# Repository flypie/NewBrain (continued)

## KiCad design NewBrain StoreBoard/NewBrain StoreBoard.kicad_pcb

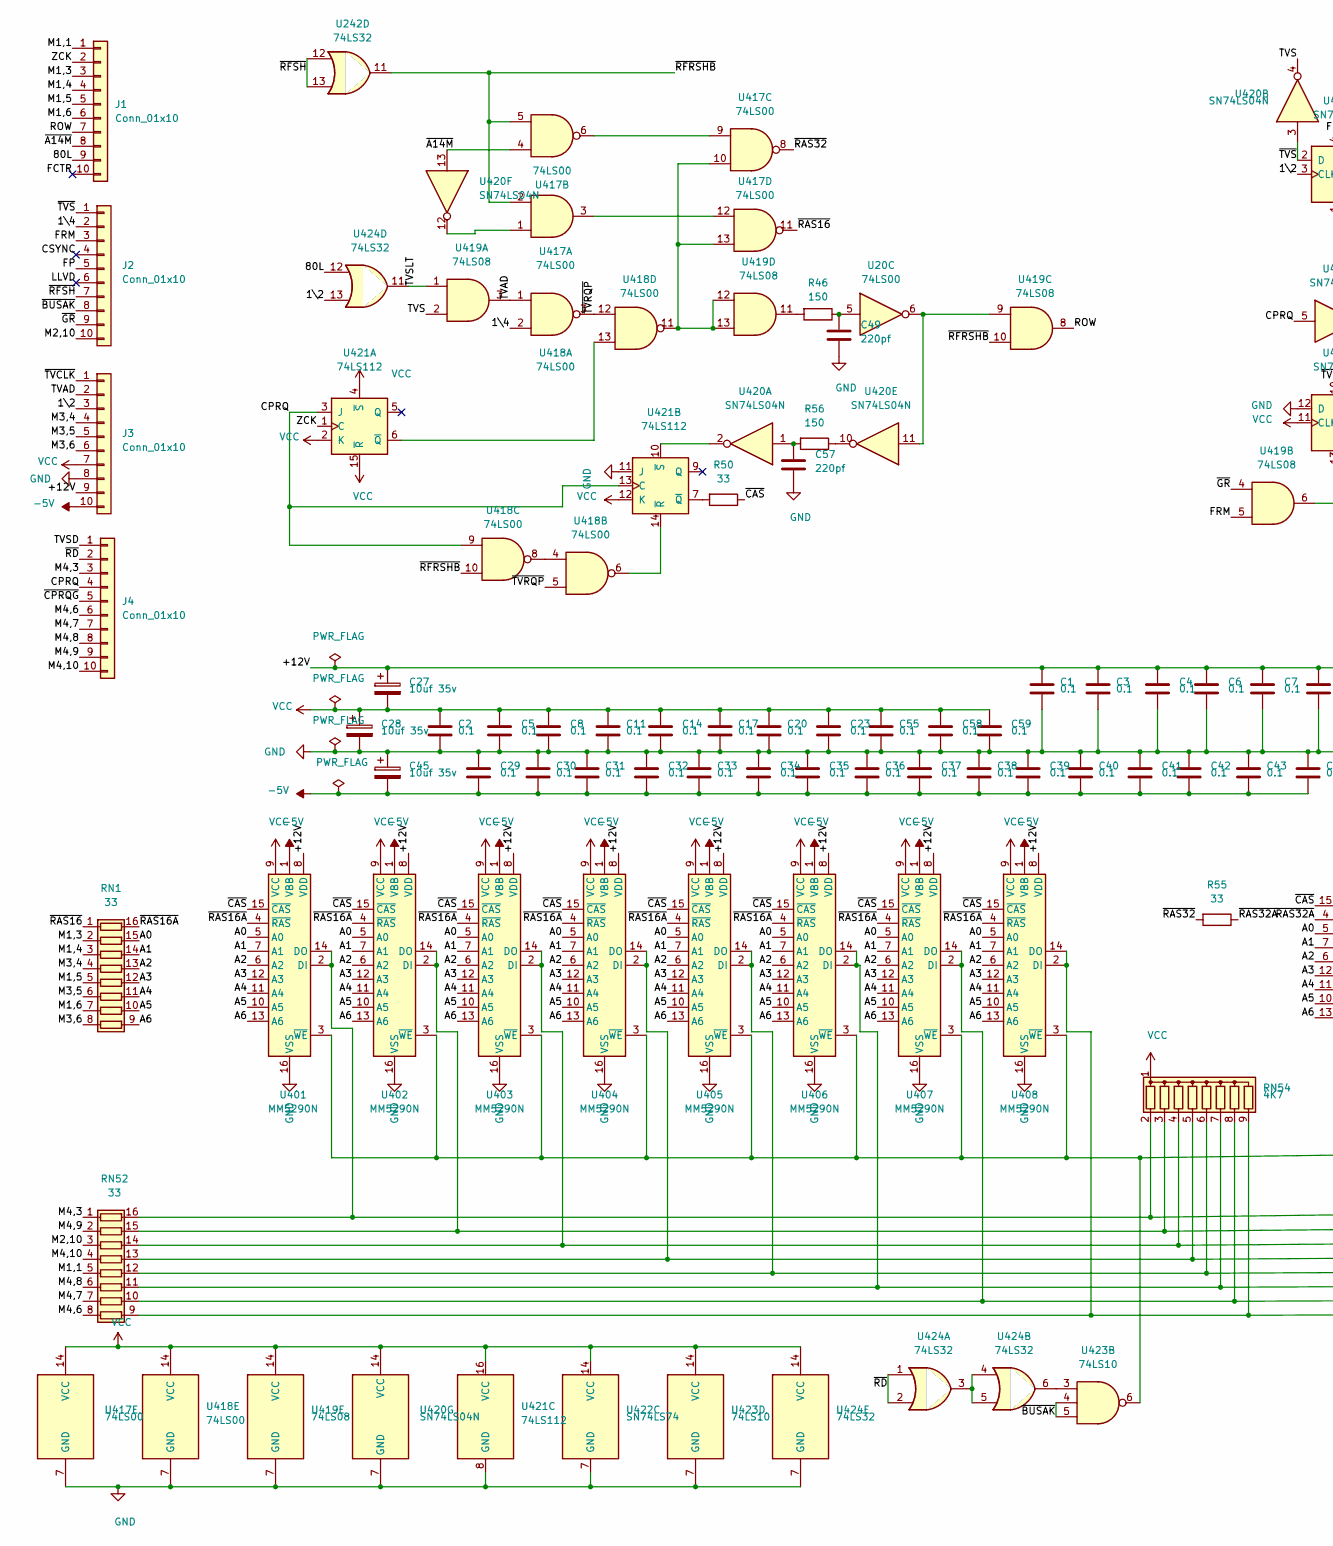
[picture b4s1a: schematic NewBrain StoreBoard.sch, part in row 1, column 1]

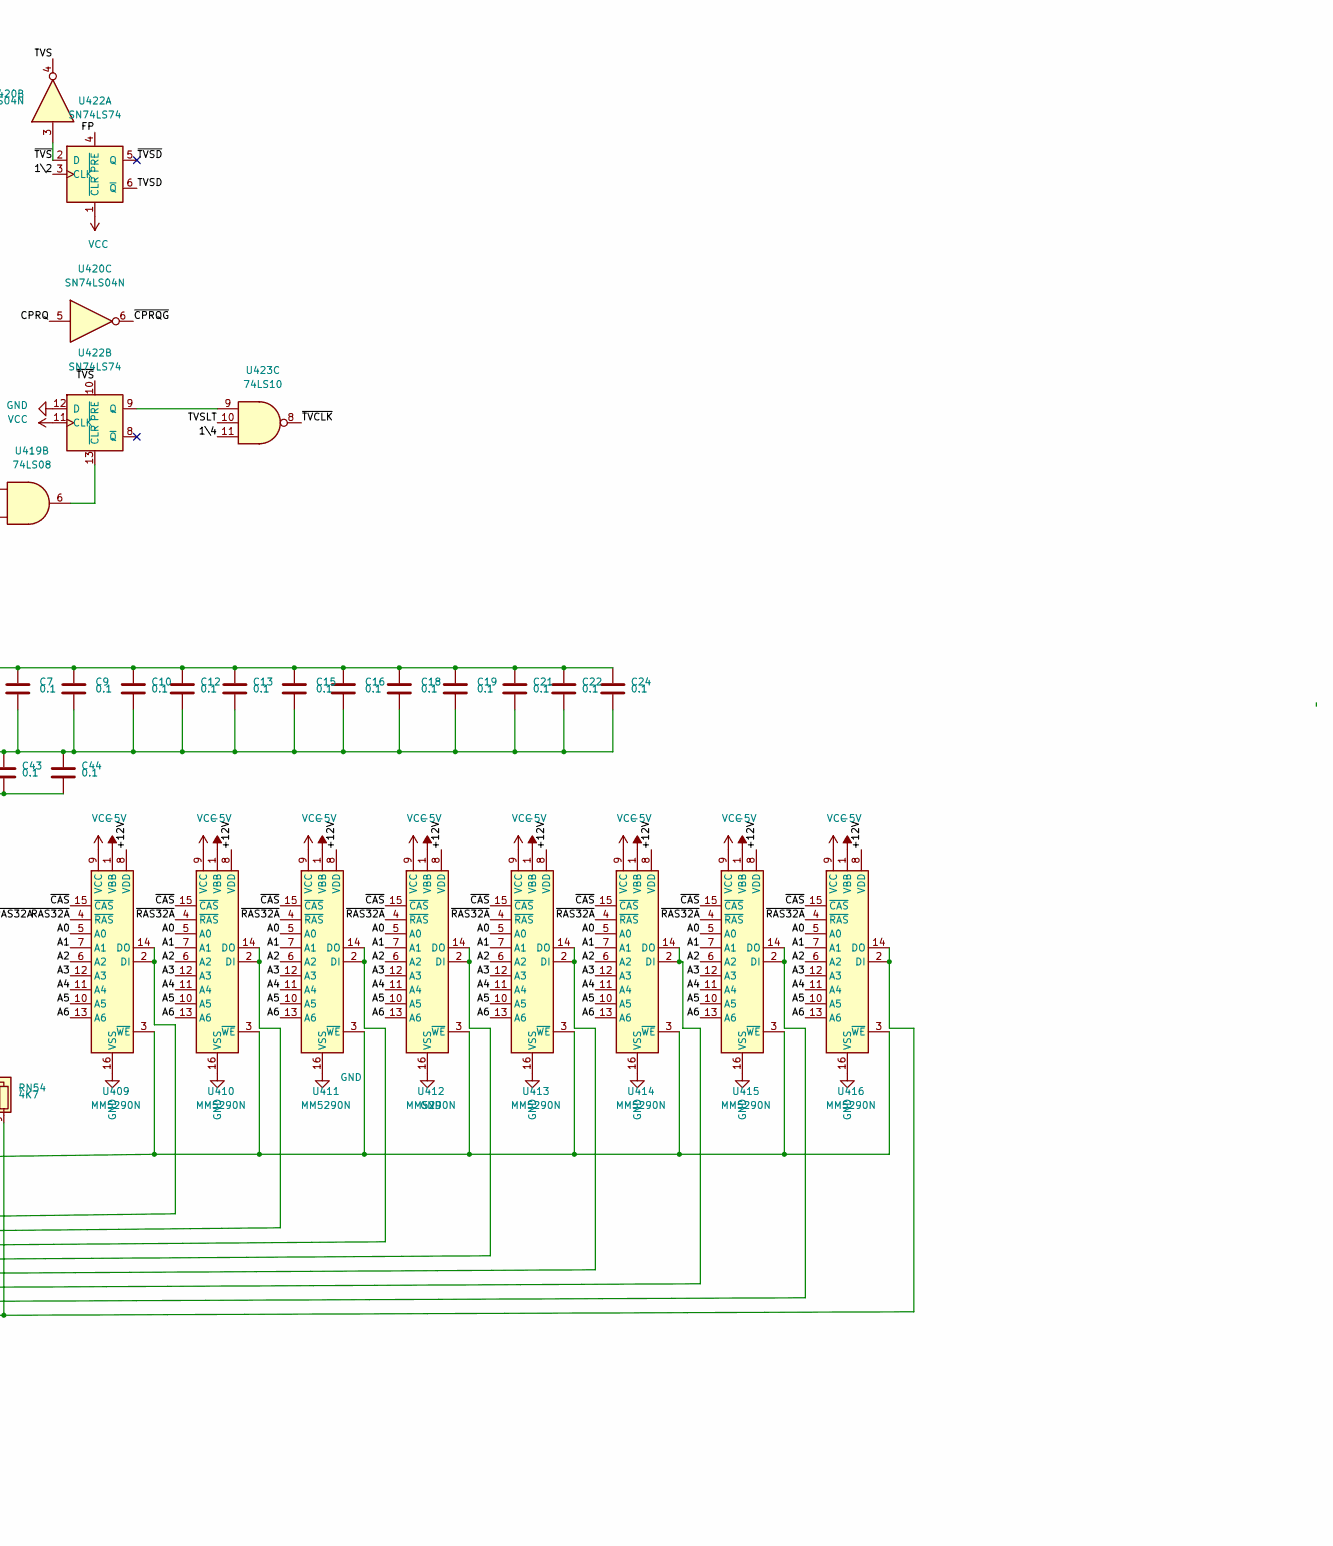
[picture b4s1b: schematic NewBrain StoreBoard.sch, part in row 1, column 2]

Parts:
C1, C2, C3, C4, C5, C6, C7, C8, C9, C10, C11, C12, C13, C14, C15, C16, C17, C18, C19, C20, C21, C22, C23, C24, C29, C30, C31, C32, C33, C34, C35, C36, C37, C38, C39, C40, C41, C42, C43, C44, C55, C58, C59: 0.1; C_Disc_D3.0mm_W1.6mm_P2.50mm
C27, C28, C45: 10uf 35v; CP_Radial_D5.0mm_P2.00mm
C49, C57: 220pf; C_Disc_D3.0mm_W1.6mm_P2.50mm
J1, J2, J3, J4: Conn_01x10; JST_EH_B10B-EH-A_1x10_P2.50mm_Vertical
R46, R56: 150; R_Axial_DIN0204_L3.6mm_D1.6mm_P2.54mm_Vertical
R50, R55: 33; R_Axial_DIN0204_L3.6mm_D1.6mm_P2.54mm_Vertical
RN1, RN52: 33; DIP-16_W7.62mm
RN54: 4K7; R_Array_SIP9
U20, U417, U418: 74LS00; DIP-16_W7.62mm
U242, U424: 74LS32; DIP-16_W7.62mm
U401, U402, U403, U404, U405, U406, U407, U408, U409, U410, U411, U412, U413, U414, U415, U416: MM5290N; DIP-16_W7.62mm
U419: 74LS08; DIP-16_W7.62mm
U420: SN74LS04N; DIP-16_W7.62mm
U421: 74LS112; DIP-16_W7.62mm
U422: SN74LS74; DIP-16_W7.62mm
U423: 74LS10; DIP-16_W7.62mm

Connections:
-5V: C29.2, C30.2, C31.2, C32.2, C33.2, C34.2, C35.2, C36.2, C37.2, C38.2, C39.2, C40.2, C41.2, C42.2, C43.2, C44.2, C45.2, J3.10, U401.1 (VBB), U402.1 (VBB), U403.1 (VBB), U404.1 (VBB), U405.1 (VBB), U406.1 (VBB), U407.1 (VBB), U408.1 (VBB), U409.1 (VBB), U410.1 (VBB), U411.1 (VBB), U412.1 (VBB), U413.1 (VBB), U414.1 (VBB), U415.1 (VBB), U416.1 (VBB)
/1\2: J3.3, U422.3 (CLK), U424.13
/1\4: J2.2, U418.2, U423.11
/80L: J1.9, U424.12
/+12V: C1.1, C3.1, C4.1, C6.1, C7.1, C9.1, C10.1, C12.1, C13.1, C15.1, C16.1, C18.1, C19.1, C21.1, C22.1, C24.1, C27.1, J3.9, U401.8 (VDD), U402.8 (VDD), U403.8 (VDD), U404.8 (VDD), U405.8 (VDD), U406.8 (VDD), U407.8 (VDD), U408.8 (VDD), U409.8 (VDD), U410.8 (VDD), U411.8 (VDD), U412.8 (VDD), U413.8 (VDD), U414.8 (VDD), U415.8 (VDD), U416.8 (VDD)
/A0: RN1.15 (R2.2), U401.5 (A0), U402.5 (A0), U403.5 (A0), U404.5 (A0), U405.5 (A0), U406.5 (A0), U407.5 (A0), U408.5 (A0), U409.5 (A0), U410.5 (A0), U411.5 (A0), U412.5 (A0), U413.5 (A0), U414.5 (A0), U415.5 (A0), U416.5 (A0)
/A1: RN1.14 (R3.2), U401.7 (A1), U402.7 (A1), U403.7 (A1), U404.7 (A1), U405.7 (A1), U406.7 (A1), U407.7 (A1), U408.7 (A1), U409.7 (A1), U410.7 (A1), U411.7 (A1), U412.7 (A1), U413.7 (A1), U414.7 (A1), U415.7 (A1), U416.7 (A1)
/A2: RN1.13 (R4.2), U401.6 (A2), U402.6 (A2), U403.6 (A2), U404.6 (A2), U405.6 (A2), U406.6 (A2), U407.6 (A2), U408.6 (A2), U409.6 (A2), U410.6 (A2), U411.6 (A2), U412.6 (A2), U413.6 (A2), U414.6 (A2), U415.6 (A2), U416.6 (A2)
/A3: RN1.12 (R5.2), U401.12 (A3), U402.12 (A3), U403.12 (A3), U404.12 (A3), U405.12 (A3), U406.12 (A3), U407.12 (A3), U408.12 (A3), U409.12 (A3), U410.12 (A3), U411.12 (A3), U412.12 (A3), U413.12 (A3), U414.12 (A3), U415.12 (A3), U416.12 (A3)
/A4: RN1.11 (R6.2), U401.11 (A4), U402.11 (A4), U403.11 (A4), U404.11 (A4), U405.11 (A4), U406.11 (A4), U407.11 (A4), U408.11 (A4), U409.11 (A4), U410.11 (A4), U411.11 (A4), U412.11 (A4), U413.11 (A4), U414.11 (A4), U415.11 (A4), U416.11 (A4)
/A5: RN1.10 (R7.2), U401.10 (A5), U402.10 (A5), U403.10 (A5), U404.10 (A5), U405.10 (A5), U406.10 (A5), U407.10 (A5), U408.10 (A5), U409.10 (A5), U410.10 (A5), U411.10 (A5), U412.10 (A5), U413.10 (A5), U414.10 (A5), U415.10 (A5), U416.10 (A5)
/A6: RN1.9 (R8.2), U401.13 (A6), U402.13 (A6), U403.13 (A6), U404.13 (A6), U405.13 (A6), U406.13 (A6), U407.13 (A6), U408.13 (A6), U409.13 (A6), U410.13 (A6), U411.13 (A6), U412.13 (A6), U413.13 (A6), U414.13 (A6), U415.13 (A6), U416.13 (A6)
/CPRQ: J4.4, U418.9, U420.5, U421.3 (J), U421.13 (C)
/CSYNC: J2.4
/FCTR: J1.10
/FP: J2.5, U422.4 (~PRE)
/FRM: J2.3, U419.5
/LLVD: J2.6
/M1,1: J1.1, RN52.5 (R5.1)
/M1,3: J1.3, RN1.2 (R2.1)
/M1,4: J1.4, RN1.3 (R3.1)
/M1,5: J1.5, RN1.5 (R5.1)
/M1,6: J1.6, RN1.7 (R7.1)
/M2,10: J2.10, RN52.3 (R3.1)
/M3,4: J3.4, RN1.4 (R4.1)
/M3,5: J3.5, RN1.6 (R6.1)
/M3,6: J3.6, RN1.8 (R8.1)
/M4,3: J4.3, RN52.1 (R1.1)
/M4,6: J4.6, RN52.8 (R8.1)
/M4,7: J4.7, RN52.7 (R7.1)
/M4,8: J4.8, RN52.6 (R6.1)
/M4,9: J4.9, RN52.2 (R2.1)
/M4,10: J4.10, RN52.4 (R4.1)
/ROW: J1.7, U419.8
/TVAD: J3.2, U418.1, U419.3
/TVS: U419.2, U420.4
/TVSD: J4.1, U422.6 (~Q)
/TVSLT: U419.1, U423.10, U424.11
/ZCK: J1.2, U421.1 (C)
/~A14M: J1.8, U417.4, U420.13
/~BUSAK: J2.8, U423.4, U423.5
/~CAS: R50.1, U401.15 (~CAS), U402.15 (~CAS), U403.15 (~CAS), U404.15 (~CAS), U405.15 (~CAS), U406.15 (~CAS), U407.15 (~CAS), U408.15 (~CAS), U409.15 (~CAS), U410.15 (~CAS), U411.15 (~CAS), U412.15 (~CAS), U413.15 (~CAS), U414.15 (~CAS), U415.15 (~CAS), U416.15 (~CAS)
/~CPRQG: J4.5, U420.6
/~GR: J2.9, U419.4
/~RAS16: RN1.1 (R1.1), U417.11
/~RAS16A: RN1.16 (R1.2), U401.4 (~RAS), U402.4 (~RAS), U403.4 (~RAS), U404.4 (~RAS), U405.4 (~RAS), U406.4 (~RAS), U407.4 (~RAS), U408.4 (~RAS)
/~RAS32: R55.2, U417.8
/~RAS32A: R55.1, U409.4 (~RAS), U410.4 (~RAS), U411.4 (~RAS), U412.4 (~RAS), U413.4 (~RAS), U414.4 (~RAS), U415.4 (~RAS), U416.4 (~RAS)
/~RD: J4.2, U424.1, U424.2
/~RFRSHB: U242.11, U417.2, U417.5, U418.10, U419.10
/~RFSH: J2.7, U242.12, U242.13
/~TVCLK: J3.1, U423.8
/~TVRQP: U418.3, U418.5, U418.12
/~TVS: J2.1, U420.3, U422.2 (D), U422.10 (~PRE)
/~TVSD: U422.5 (Q)
GND: C1.2, C2.2, C3.2, C4.2, C5.2, C6.2, C7.2, C8.2, C9.2, C10.2, C11.2, C12.2, C13.2, C14.2, C15.2, C16.2, C17.2, C18.2, C19.2, C20.2, C21.2, C22.2, C23.2, C24.2, C28.2, C29.1, C30.1, C31.1, C32.1, C33.1, C34.1, C35.1, C36.1, C37.1, C38.1, C39.1, C40.1, C41.1, C42.1, C43.1, C44.1, C45.1, C49.2, C55.2, C57.2, C58.2, C59.2, J3.8, U401.16 (VSS), U402.16 (VSS), U403.16 (VSS), U404.16 (VSS), U405.16 (VSS), U406.16 (VSS), U407.16 (VSS), U408.16 (VSS), U409.16 (VSS), U410.16 (VSS), U411.16 (VSS), U412.16 (VSS), U413.16 (VSS), U414.16 (VSS), U415.16 (VSS), U416.16 (VSS), U417.7 (GND), U418.7 (GND), U419.7 (GND), U420.7 (GND), U421.8 (GND), U421.11 (J), U422.7 (GND), U422.12 (D), U423.7 (GND), U424.7 (GND)
unnamed: C49.1, R46.1, U20.5
unnamed: C57.1, R56.2, U420.1
unnamed: R46.2, U419.11
unnamed: R50.2, U421.7 (~Q)
unnamed: R56.1, U420.10
unnamed: RN52.9 (R8.2), RN54.9 (R8), U408.2 (DI), U408.14 (DO), U416.2 (DI), U416.14 (DO)
unnamed: RN52.10 (R7.2), RN54.8 (R7), U407.2 (DI), U407.14 (DO), U415.2 (DI), U415.14 (DO)
unnamed: RN52.11 (R6.2), RN54.7 (R6), U406.2 (DI), U406.14 (DO), U414.2 (DI), U414.14 (DO)
unnamed: RN52.12 (R5.2), RN54.6 (R5), U405.2 (DI), U405.14 (DO), U413.2 (DI), U413.14 (DO)
unnamed: RN52.13 (R4.2), RN54.5 (R4), U404.2 (DI), U404.14 (DO), U412.2 (DI), U412.14 (DO)
unnamed: RN52.14 (R3.2), RN54.4 (R3), U403.2 (DI), U403.14 (DO), U411.2 (DI), U411.14 (DO)
unnamed: RN52.15 (R2.2), RN54.3 (R2), U402.2 (DI), U402.14 (DO), U410.2 (DI), U410.14 (DO)
unnamed: RN52.16 (R1.2), RN54.2 (R1), U401.2 (DI), U401.14 (DO), U409.2 (DI), U409.14 (DO)
unnamed: U20.6, U419.9, U420.11
unnamed: U401.3 (~WE), U402.3 (~WE), U403.3 (~WE), U404.3 (~WE), U405.3 (~WE), U406.3 (~WE), U407.3 (~WE), U408.3 (~WE), U409.3 (~WE), U410.3 (~WE), U411.3 (~WE), U412.3 (~WE), U413.3 (~WE), U414.3 (~WE), U415.3 (~WE), U416.3 (~WE), U423.6
unnamed: U417.1, U420.12
unnamed: U417.6, U417.9
unnamed: U417.10, U417.13, U418.11, U419.12, U419.13
unnamed: U417.3, U417.12
unnamed: U418.4, U418.8
unnamed: U418.6, U421.14 (~R)
unnamed: U418.13, U421.6 (~Q)
unnamed: U419.6, U422.13 (~CLR)
unnamed: U420.2, U421.10 (~S)
unnamed: U422.9 (Q), U423.9
unnamed: U423.3, U424.6
unnamed: U424.3, U424.4, U424.5
VCC: C2.1, C5.1, C8.1, C11.1, C14.1, C17.1, C20.1, C23.1, C27.2, C28.1, C55.1, C58.1, C59.1, J3.7, RN54.1 (common), U401.9 (VCC), U402.9 (VCC), U403.9 (VCC), U404.9 (VCC), U405.9 (VCC), U406.9 (VCC), U407.9 (VCC), U408.9 (VCC), U409.9 (VCC), U410.9 (VCC), U411.9 (VCC), U412.9 (VCC), U413.9 (VCC), U414.9 (VCC), U415.9 (VCC), U416.9 (VCC), U417.14 (VCC), U418.14 (VCC), U419.14 (VCC), U420.14 (VCC), U421.2 (K), U421.4 (~S), U421.12 (K), U421.15 (~R), U421.16 (VCC), U422.1 (~CLR), U422.11 (CLK), U422.14 (VCC), U423.14 (VCC), U424.14 (VCC)

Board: 2 copper layers, 85 parts (0 on the bottom side), 80 nets, no tracks yet.

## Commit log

2020-06-15 Initial Post.
2020-06-15 Add some more.
2020-06-16 First Drawing first draft.
2020-06-16 Start sheet TWO.
2020-06-17 Next stage of page 2.
2020-06-17 Complete most of drawing 2.
2020-06-18 Minor label changes.
2020-06-18 Some more link fixes now below 100 warnings.
2020-06-18 More Label fixing. Down to 16 Warnings. Lots of devie Labels and balues wrong.
2020-06-19 Resolve inconsistencies in circuit diagram buy following traces.
    Resistor name used twice temp solution add a and b to name.
2020-06-20 Resolve diplicate R28 from drawings, one is R30 a pullup resistor connected.
    Trace 4 pins on memory board header.
    Add aligned PCB igmes with alpha channel and beginings of annotated image.
2020-06-22 Create LICENSE
2020-06-22 Create LICENSE (#1)
2020-06-22 Rearrange directories.
2020-06-22 Add StoreBoard Schematic. It is dynamic RAM with Strobed address.
2020-06-23 Add Keyboard A.
    The Label in the diagram this is based on says Keyboard AD but there is no display that is in the Kayboard A Diagram. The Wiring for the plug does not seem to agre with the main board.
2020-06-23 Add PSU. Good luck trying to find a Transformer that works to those specs.
2020-06-24 Complete Expansion Port.
2020-06-26 UPdates add links and fix values add smoothing capacitors.
